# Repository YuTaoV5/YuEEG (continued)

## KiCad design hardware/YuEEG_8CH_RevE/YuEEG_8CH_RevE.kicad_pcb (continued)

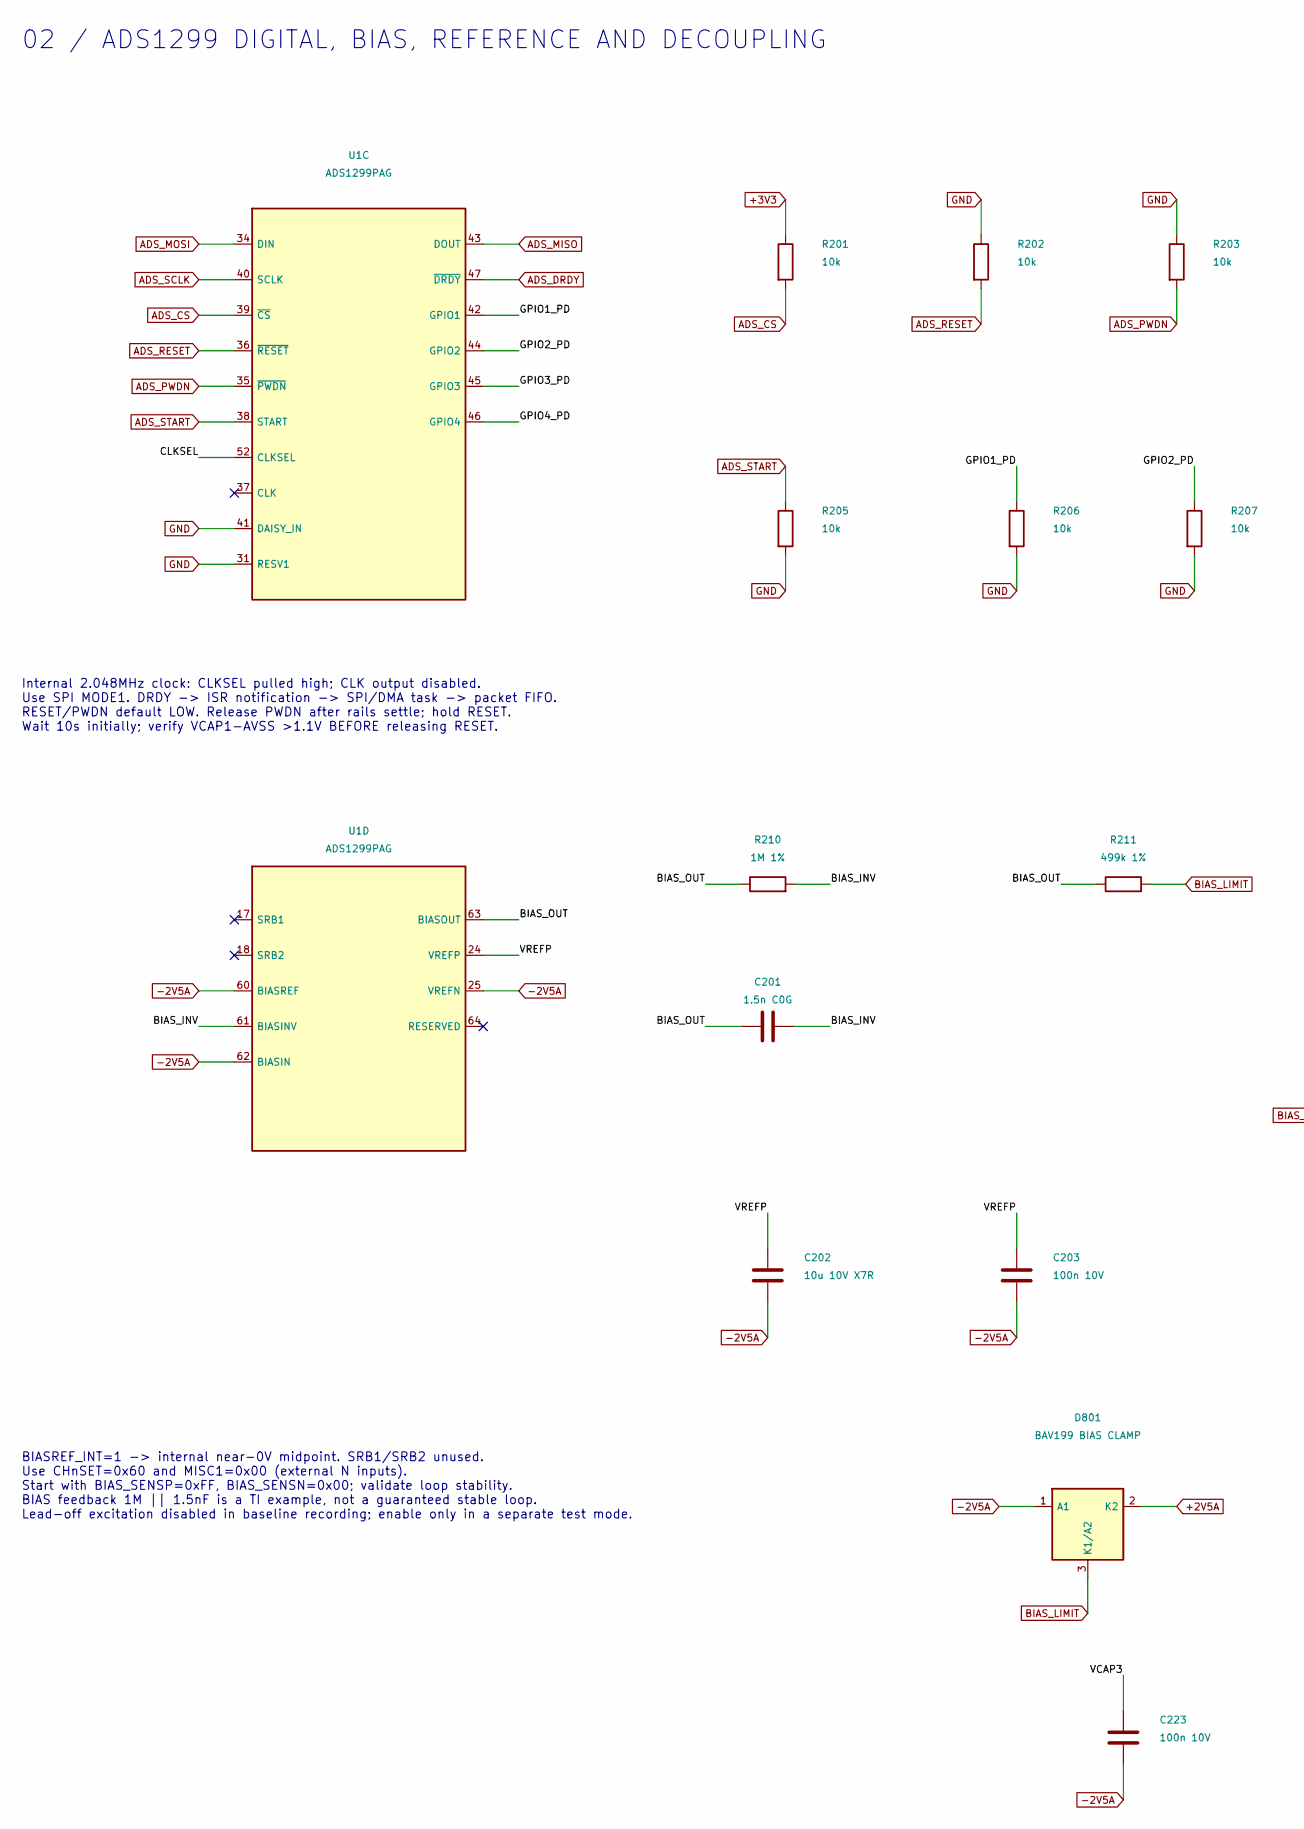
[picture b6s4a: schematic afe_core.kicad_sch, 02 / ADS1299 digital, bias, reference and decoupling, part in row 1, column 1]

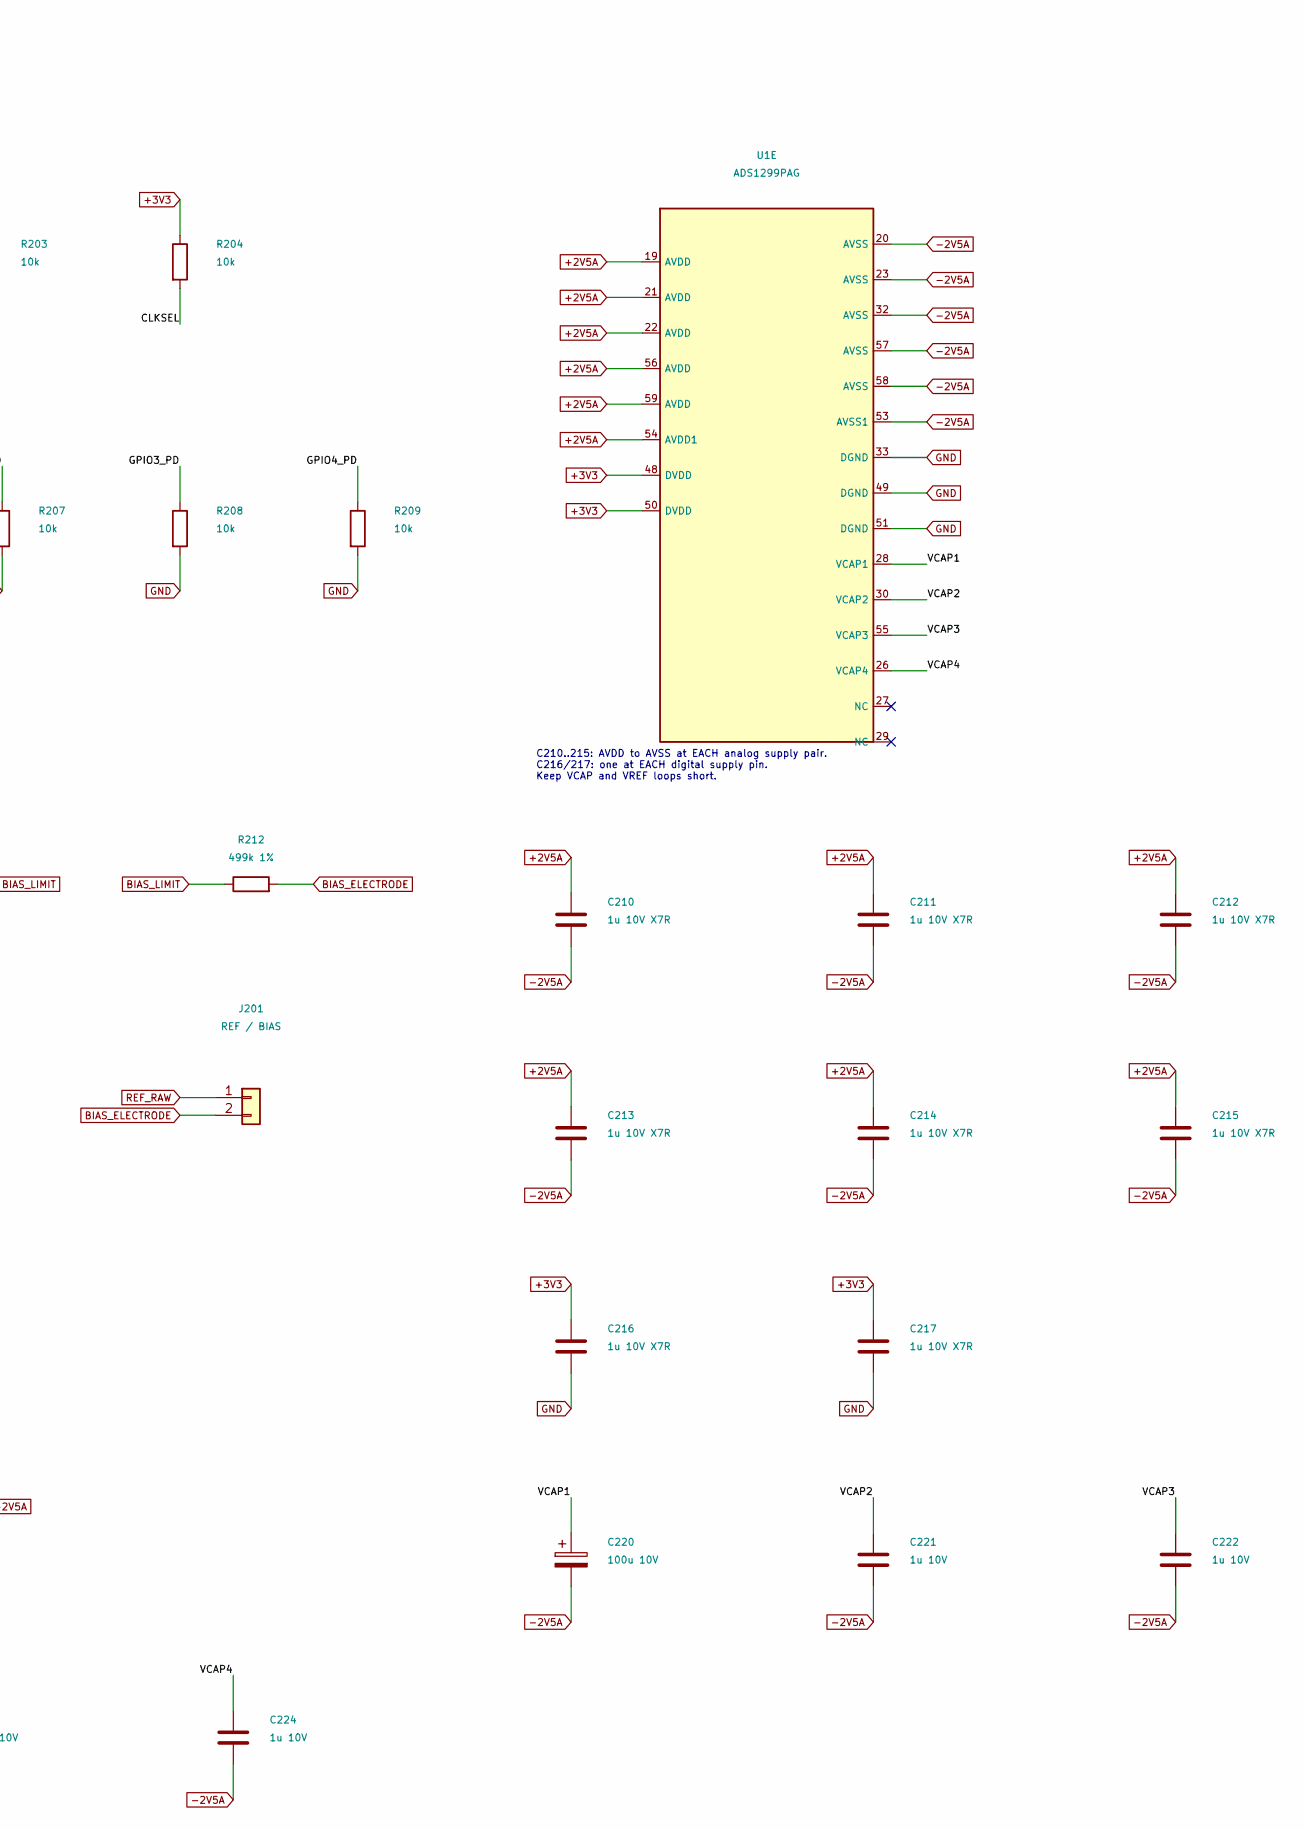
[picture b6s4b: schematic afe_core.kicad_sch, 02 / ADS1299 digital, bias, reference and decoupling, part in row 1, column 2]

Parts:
C201: 1.5n C0G; C_0603_1608Metric
C202: 10u 10V X7R; C_0805_2012Metric
C203, C223: 100n 10V; C_0603_1608Metric
C210, C211, C212, C213, C214, C215, C216, C217: 1u 10V X7R; C_0603_1608Metric
C220: 100u 10V; CP_Elec_6.3x7.7
C221, C222, C224: 1u 10V; C_0603_1608Metric
D801: BAV199 BIAS CLAMP; SOT-23
J201: REF / BIAS; PinHeader_1x02_P2.54mm_Vertical
R201, R202, R203, R204, R205, R206, R207, R208, R209: 10k; R_0603_1608Metric
R210: 1M 1%; R_0603_1608Metric
R211, R212: 499k 1%; R_0603_1608Metric
U1: ADS1299PAG; TQFP-64_10x10mm_P0.5mm

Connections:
+2V5A: C210.1, C211.1, C212.1, C213.1, C214.1, C215.1, D801.2 (K2), U1.19 (AVDD), U1.21 (AVDD), U1.22 (AVDD), U1.54 (AVDD1), U1.56 (AVDD), U1.59 (AVDD); also elsewhere on the board
+3V3: C216.1, C217.1, R201.1, R204.1, U1.48 (DVDD), U1.50 (DVDD); also elsewhere on the board
-2V5A: C202.2, C203.2, C210.2, C211.2, C212.2, C213.2, C214.2, C215.2, C220.2, C221.2, C222.2, C223.2, C224.2, D801.1 (A1), U1.20 (AVSS), U1.23 (AVSS), U1.25 (VREFN), U1.32 (AVSS), U1.53 (AVSS1), U1.57 (AVSS), U1.58 (AVSS), U1.60 (BIASREF), U1.62 (BIASIN); also elsewhere on the board
/02 / ADS1299 digital, bias, reference and decoupling/BIAS_INV: C201.2, R210.2, U1.61 (BIASINV)
/02 / ADS1299 digital, bias, reference and decoupling/BIAS_OUT: C201.1, R210.1, R211.1, U1.63 (BIASOUT)
/02 / ADS1299 digital, bias, reference and decoupling/CLKSEL: R204.2, U1.52 (CLKSEL)
/02 / ADS1299 digital, bias, reference and decoupling/GPIO1_PD: R206.1, U1.42 (GPIO1)
/02 / ADS1299 digital, bias, reference and decoupling/GPIO2_PD: R207.1, U1.44 (GPIO2)
/02 / ADS1299 digital, bias, reference and decoupling/GPIO3_PD: R208.1, U1.45 (GPIO3)
/02 / ADS1299 digital, bias, reference and decoupling/GPIO4_PD: R209.1, U1.46 (GPIO4)
/02 / ADS1299 digital, bias, reference and decoupling/VCAP1: C220.1, U1.28 (VCAP1)
/02 / ADS1299 digital, bias, reference and decoupling/VCAP2: C221.1, U1.30 (VCAP2)
/02 / ADS1299 digital, bias, reference and decoupling/VCAP3: C222.1, C223.1, U1.55 (VCAP3)
/02 / ADS1299 digital, bias, reference and decoupling/VCAP4: C224.1, U1.26 (VCAP4)
/02 / ADS1299 digital, bias, reference and decoupling/VREFP: C202.1, C203.1, U1.24 (VREFP)
ADS_CS: R201.2, U1.39 (~CS); also elsewhere on the board
ADS_DRDY: U1.47 (~DRDY); also elsewhere on the board
ADS_MISO: U1.43 (DOUT); also elsewhere on the board
ADS_MOSI: U1.34 (DIN); also elsewhere on the board
ADS_PWDN: R203.2, U1.35 (~PWDN); also elsewhere on the board
ADS_RESET: R202.2, U1.36 (~RESET); also elsewhere on the board
ADS_SCLK: U1.40 (SCLK); also elsewhere on the board
ADS_START: R205.1, U1.38 (START); also elsewhere on the board
BIAS_ELECTRODE: J201.2, R212.2
BIAS_LIMIT: D801.3 (K1/A2), R211.2, R212.1
GND: C216.2, C217.2, R202.1, R203.1, R205.2, R206.2, R207.2, R208.2, R209.2, U1.31 (RESV1), U1.33 (DGND), U1.41 (DAISY_IN), U1.49 (DGND), U1.51 (DGND); also elsewhere on the board
REF_RAW: J201.1; also elsewhere on the board

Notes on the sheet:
02 / ADS1299 DIGITAL, BIAS, REFERENCE AND DECOUPLING
Internal 2.048MHz clock: CLKSEL pulled high; CLK output disabled. Use SPI MODE1. DRDY -> ISR notification -> SPI/DMA task -> packet FIFO. RESET/PWDN default LOW. Release PWDN after rails settle; hold RESET. Wait 10s initially; verify VCAP1-AVSS >1.1V BEFORE releasing RESET.
BIASREF_INT=1 -> internal near-0V midpoint. SRB1/SRB2 unused. Use CHnSET=0x60 and MISC1=0x00 (external N inputs). Start with BIAS_SENSP=0xFF, BIAS_SENSN=0x00; validate loop stability. BIAS feedback 1M || 1.5nF is a TI example, not a guaranteed stable loop. Lead-off excitation disabled in baseline r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
C210..215: AVDD to AVSS at EACH analog supply pair. C216/217: one at EACH digital supply pin. Keep VCAP and VREF loops short.

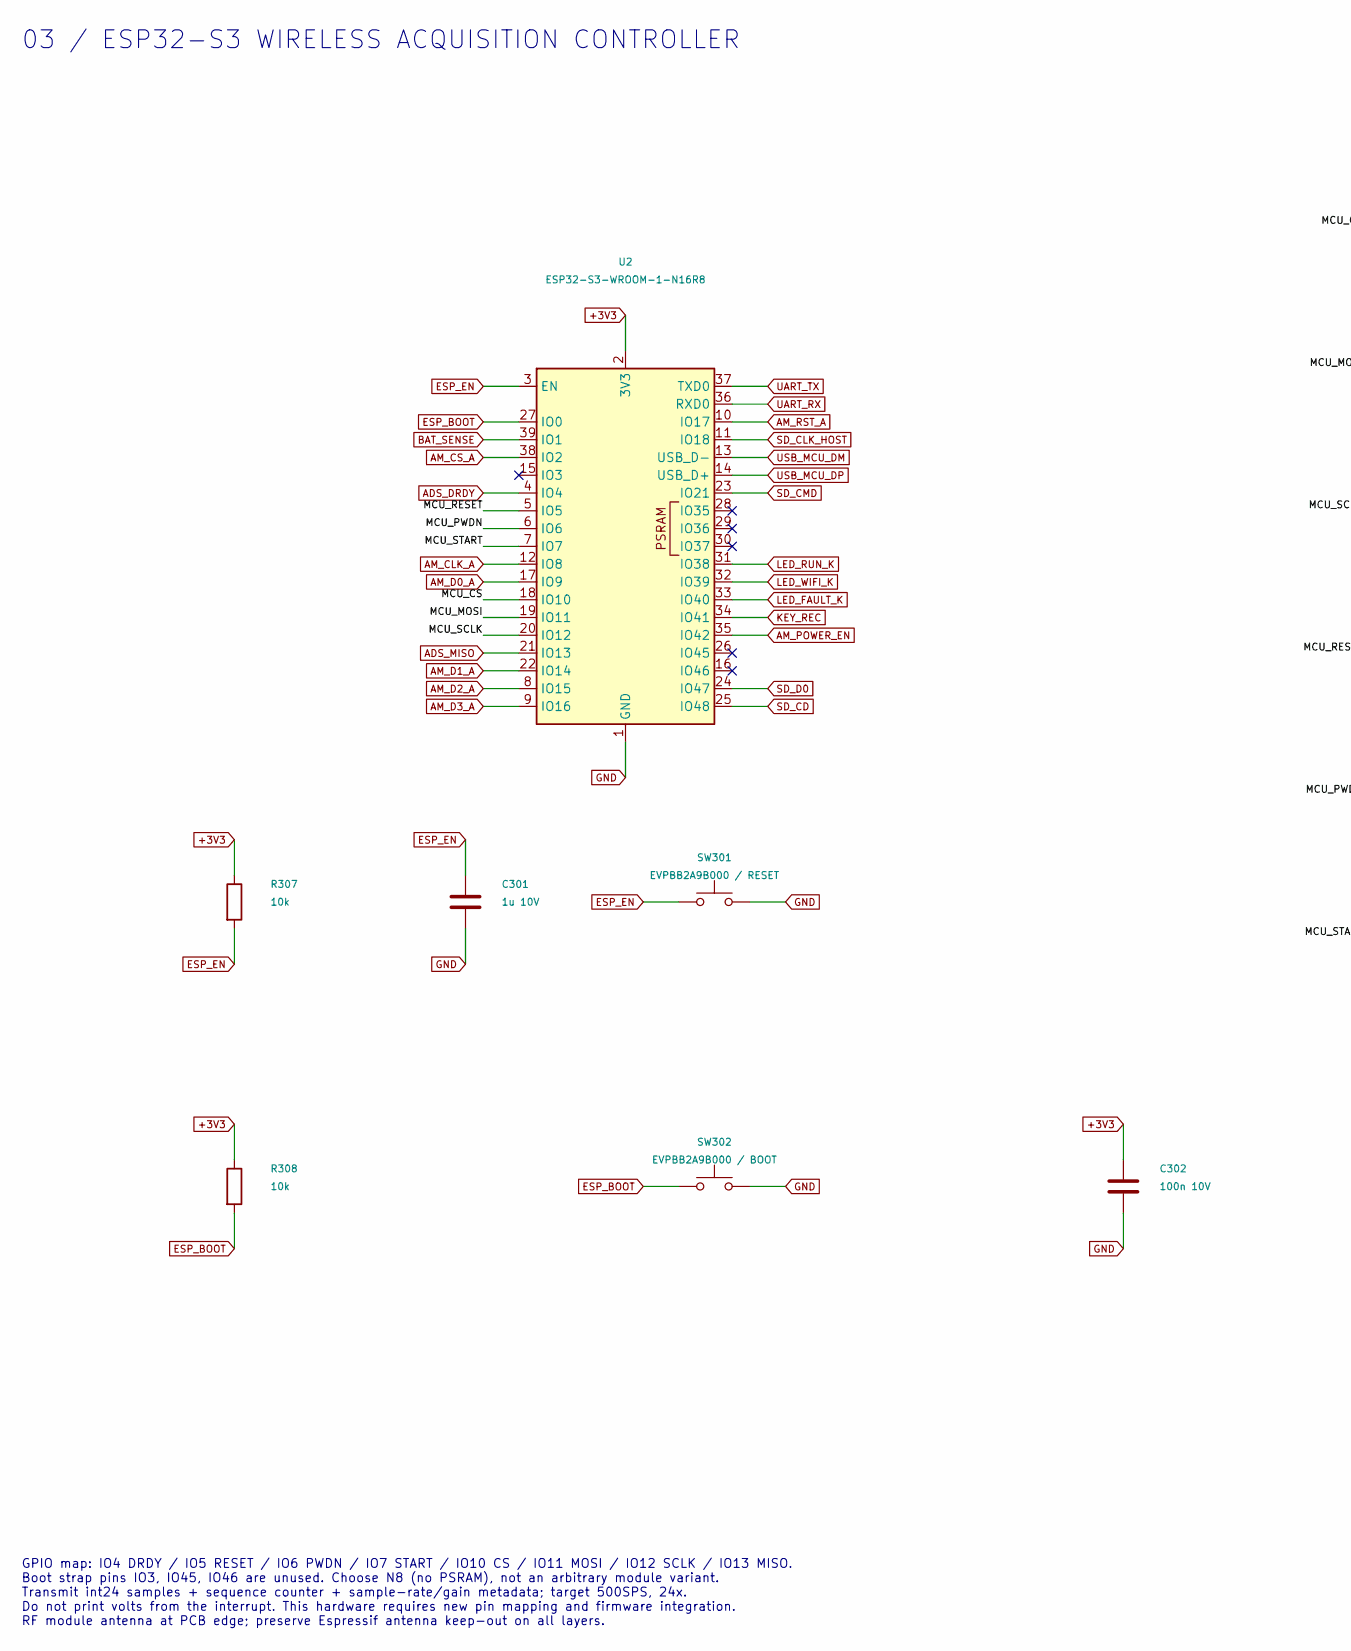
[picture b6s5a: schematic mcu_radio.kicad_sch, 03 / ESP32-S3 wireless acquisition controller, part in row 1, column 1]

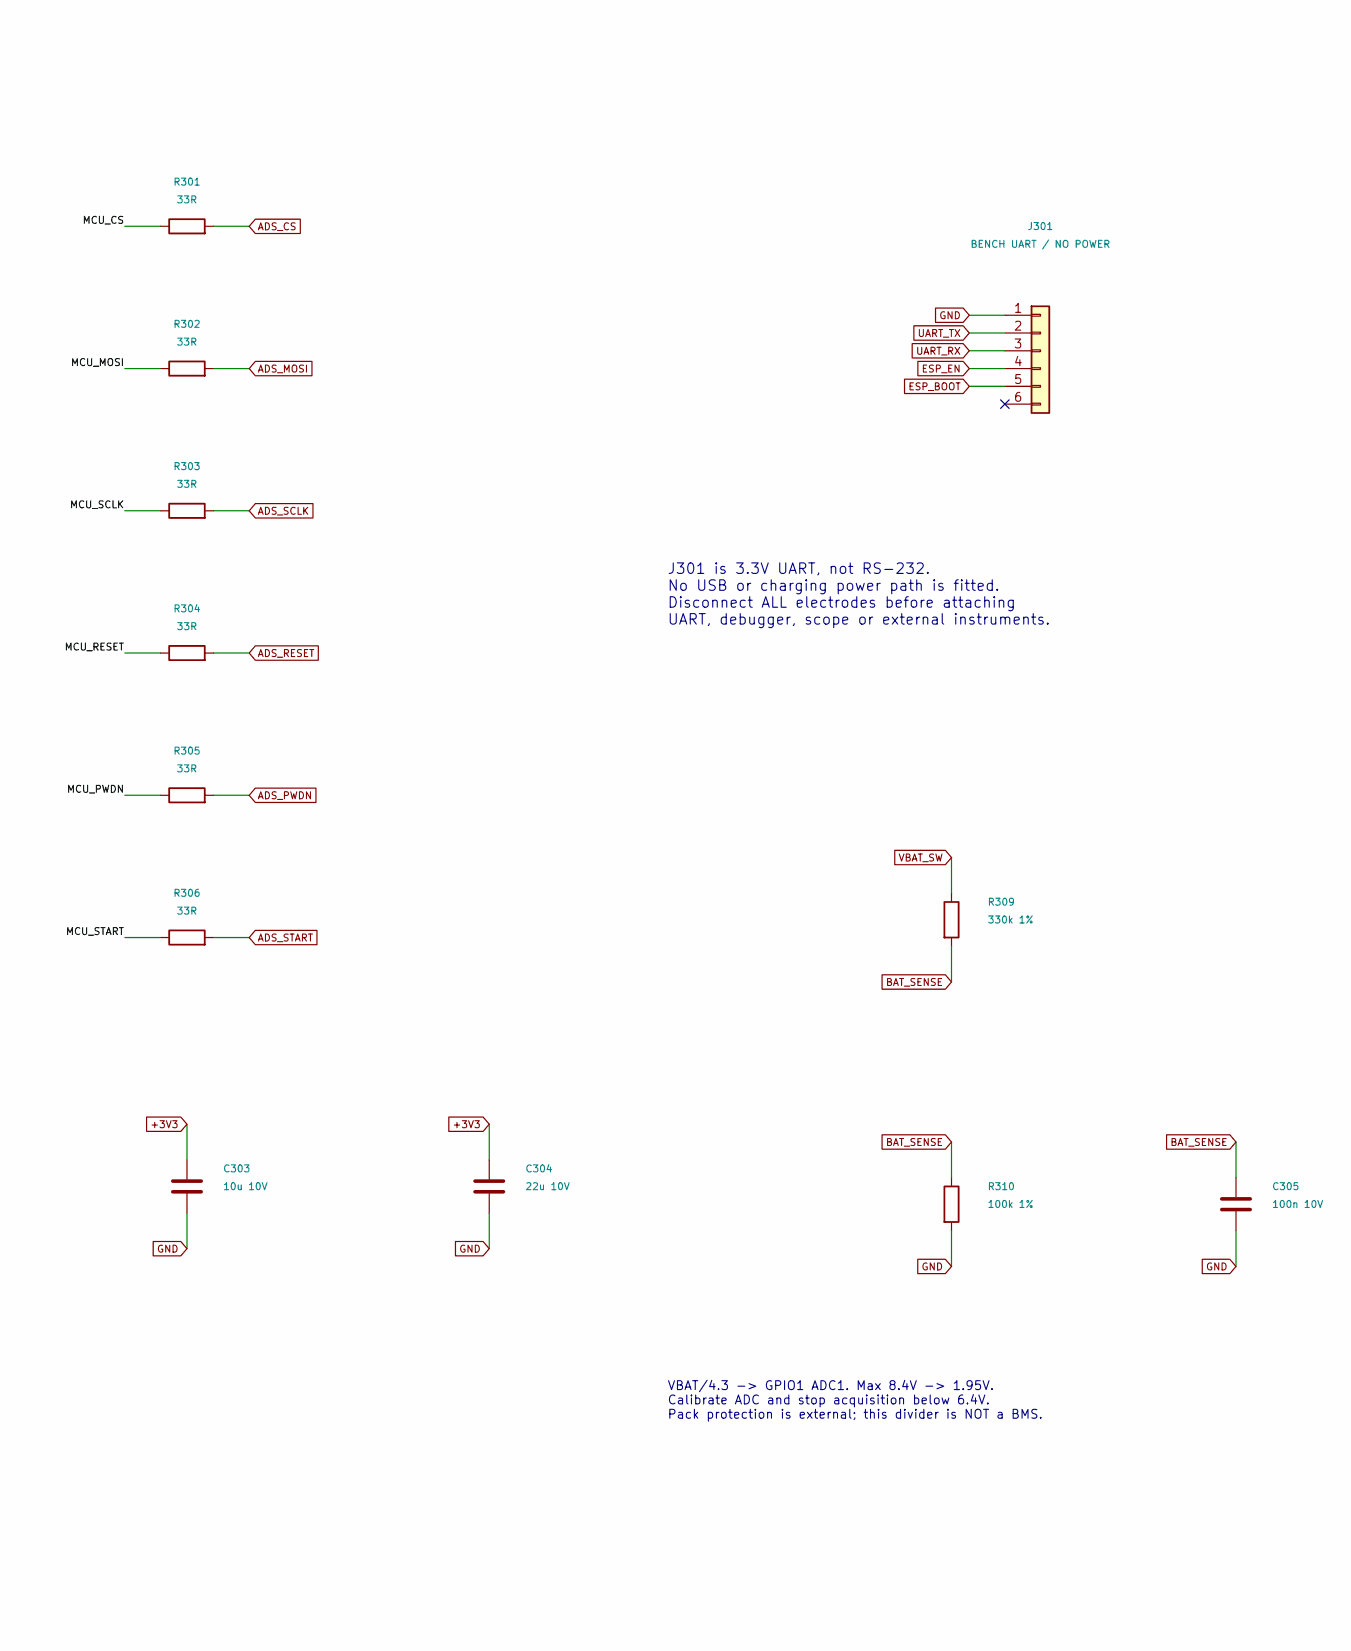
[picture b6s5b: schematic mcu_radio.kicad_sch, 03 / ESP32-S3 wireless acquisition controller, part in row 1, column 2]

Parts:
C301: 1u 10V; C_0603_1608Metric
C302: 100n 10V; C_0805_2012Metric
C303: 10u 10V; C_0805_2012Metric
C304: 22u 10V; C_0805_2012Metric
C305: 100n 10V; C_0603_1608Metric
J301: BENCH UART / NO POWER; PinHeader_1x06_P2.54mm_Vertical
R301, R302, R303, R304, R305, R306: 33R; R_0603_1608Metric
R307, R308: 10k; R_0603_1608Metric
R309: 330k 1%; R_0603_1608Metric
R310: 100k 1%; R_0603_1608Metric
SW301: EVPBB2A9B000 / RESET; EVPBB_2p6x1p6_H0p53
SW302: EVPBB2A9B000 / BOOT; EVPBB_2p6x1p6_H0p53
U2: ESP32-S3-WROOM-1-N16R8; ESP32-S3-WROOM-1

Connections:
+3V3: C302.1, C303.1, C304.1, R307.1, R308.1, U2.2 (3V3); also elsewhere on the board
/03 / ESP32-S3 wireless acquisition controller/MCU_CS: R301.1, U2.18 (IO10)
/03 / ESP32-S3 wireless acquisition controller/MCU_MOSI: R302.1, U2.19 (IO11)
/03 / ESP32-S3 wireless acquisition controller/MCU_PWDN: R305.1, U2.6 (IO6)
/03 / ESP32-S3 wireless acquisition controller/MCU_RESET: R304.1, U2.5 (IO5)
/03 / ESP32-S3 wireless acquisition controller/MCU_SCLK: R303.1, U2.20 (IO12)
/03 / ESP32-S3 wireless acquisition controller/MCU_START: R306.1, U2.7 (IO7)
ADS_CS: R301.2; also elsewhere on the board
ADS_DRDY: U2.4 (IO4); also elsewhere on the board
ADS_MISO: U2.21 (IO13); also elsewhere on the board
ADS_MOSI: R302.2; also elsewhere on the board
ADS_PWDN: R305.2; also elsewhere on the board
ADS_RESET: R304.2; also elsewhere on the board
ADS_SCLK: R303.2; also elsewhere on the board
ADS_START: R306.2; also elsewhere on the board
AM_CLK_A: U2.12 (IO8); also elsewhere on the board
AM_CS_A: U2.38 (IO2); also elsewhere on the board
AM_D0_A: U2.17 (IO9); also elsewhere on the board
AM_D1_A: U2.22 (IO14); also elsewhere on the board
AM_D2_A: U2.8 (IO15); also elsewhere on the board
AM_D3_A: U2.9 (IO16); also elsewhere on the board
AM_POWER_EN: U2.35 (IO42); also elsewhere on the board
AM_RST_A: U2.10 (IO17); also elsewhere on the board
BAT_SENSE: C305.1, R309.2, R310.1, U2.39 (IO1)
ESP_BOOT: J301.5, R308.2, SW302.1, U2.27 (IO0)
ESP_EN: C301.1, J301.4, R307.2, SW301.1, U2.3 (EN)
GND: C301.2, C302.2, C303.2, C304.2, C305.2, J301.1, R310.2, SW301.2, SW302.2, U2.1 (GND), U2.40 (GND), U2.41 (GND); also elsewhere on the board
KEY_REC: U2.34 (IO41); also elsewhere on the board
LED_FAULT_K: U2.33 (IO40); also elsewhere on the board
LED_RUN_K: U2.31 (IO38); also elsewhere on the board
LED_WIFI_K: U2.32 (IO39); also elsewhere on the board
SD_CD: U2.25 (IO48); also elsewhere on the board
SD_CLK_HOST: U2.11 (IO18); also elsewhere on the board
SD_CMD: U2.23 (IO21); also elsewhere on the board
SD_D0: U2.24 (IO47); also elsewhere on the board
UART_RX: J301.3, U2.36 (RXD0)
UART_TX: J301.2, U2.37 (TXD0)
USB_MCU_DM: U2.13 (USB_D-); also elsewhere on the board
USB_MCU_DP: U2.14 (USB_D+); also elsewhere on the board
VBAT_SW: R309.1; also elsewhere on the board

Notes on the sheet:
03 / ESP32-S3 WIRELESS ACQUISITION CONTROLLER
J301 is 3.3V UART, not RS-232. No USB or charging power path is fitted. Disconnect ALL electrodes before attaching UART, debugger, scope or external instruments.
VBAT/4.3 -> GPIO1 ADC1. Max 8.4V -> 1.95V. Calibrate ADC and stop acquisition below 6.4V. Pack protection is external; this divider is NOT a BMS.
GPIO map: IO4 DRDY / IO5 RESET / IO6 PWDN / IO7 START / IO10 CS / IO11 MOSI / IO12 SCLK / IO13 MISO. Boot strap pins IO3, IO45, IO46 are unused. Choose N8 (no PSRAM), not an arbitrary module variant. Transmit int24 samples + sequence counter + sample-rate/gain metadata; target 500SPS, 24x. Do not p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

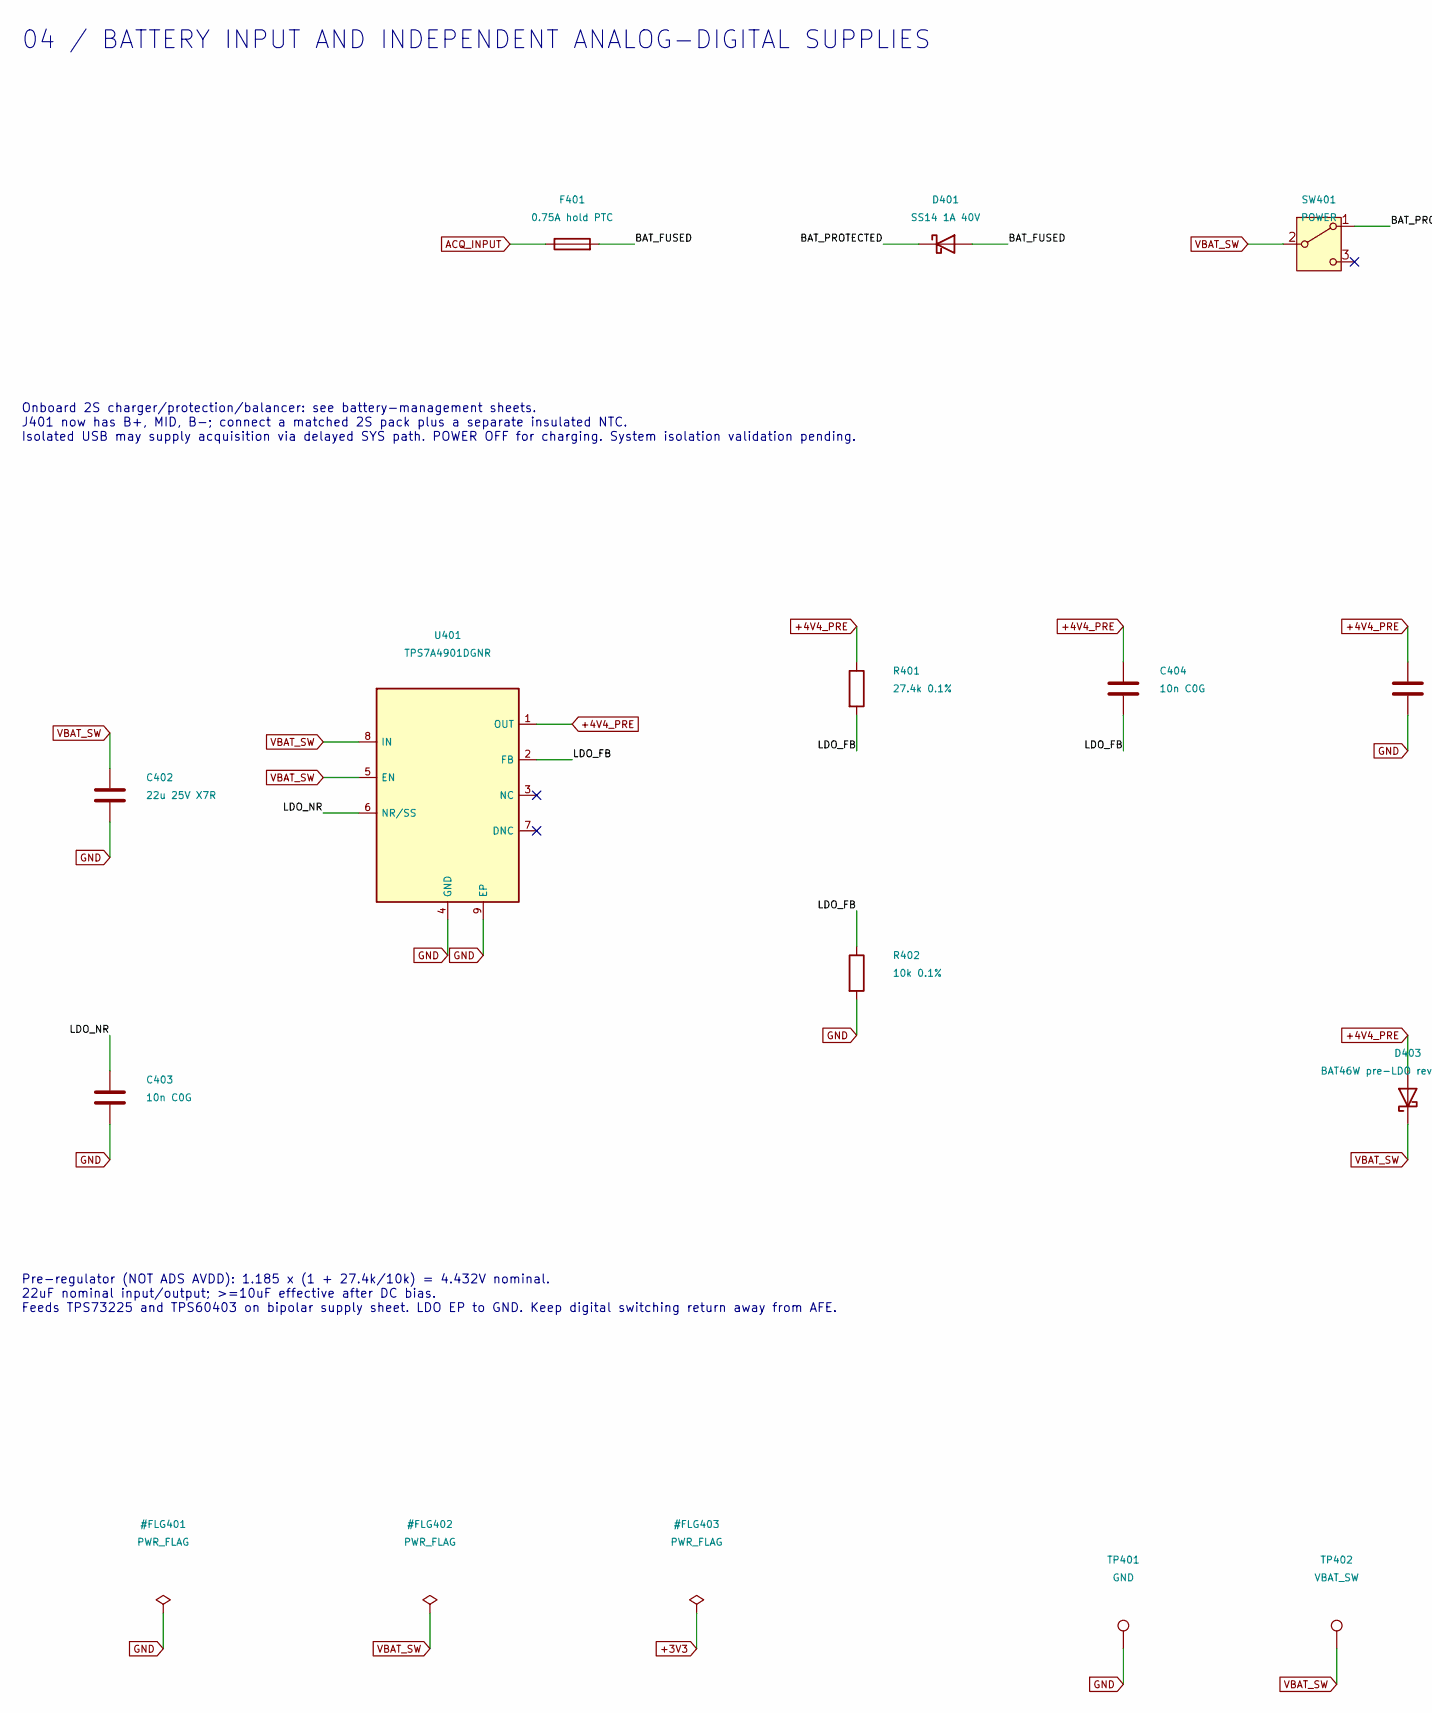
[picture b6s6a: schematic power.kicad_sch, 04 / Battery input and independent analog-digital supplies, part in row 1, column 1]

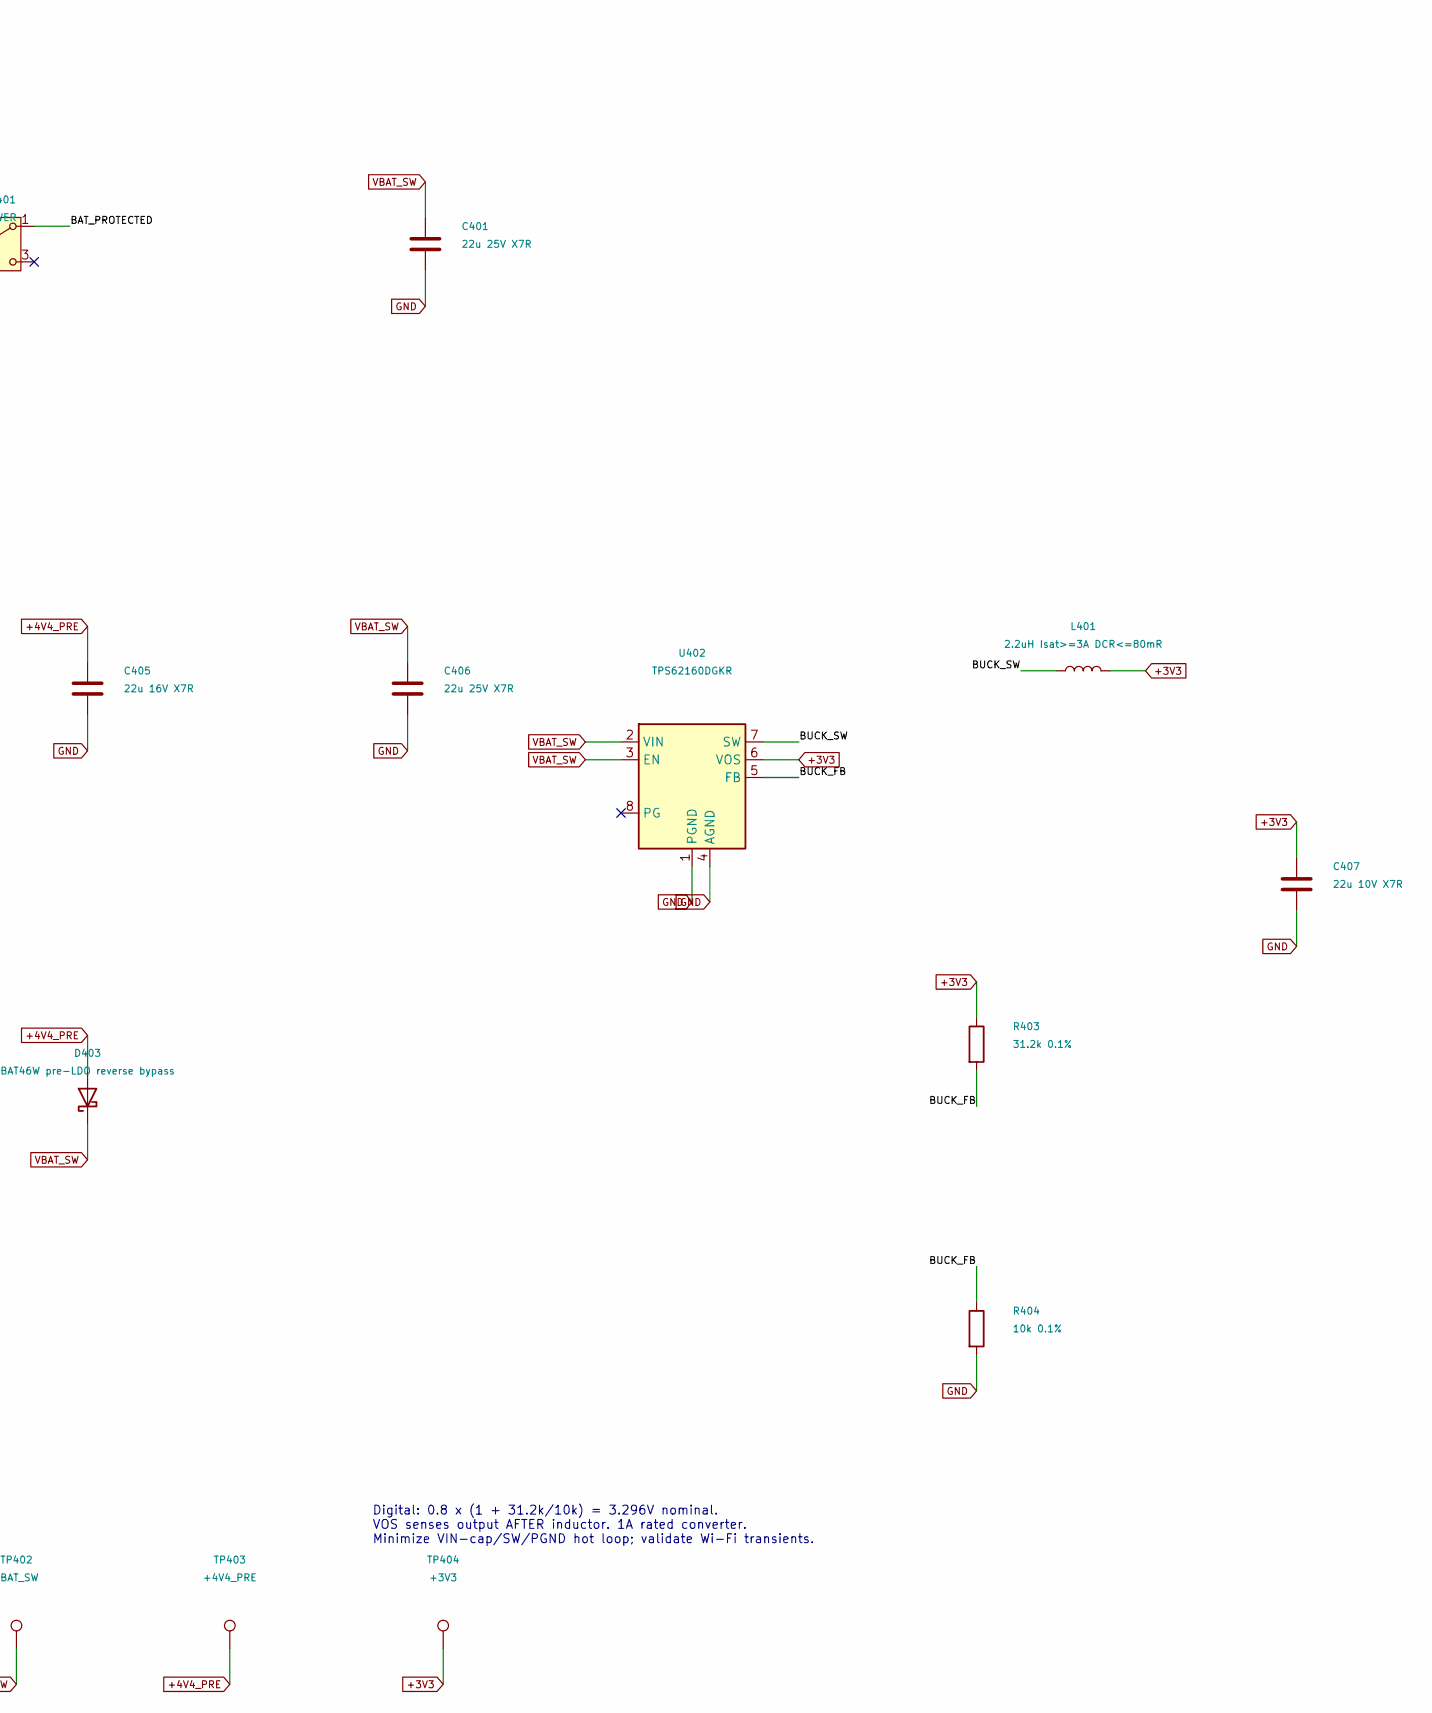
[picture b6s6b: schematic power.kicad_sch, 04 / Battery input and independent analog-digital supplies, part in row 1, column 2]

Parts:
C401, C402, C406: 22u 25V X7R; C_1206_3216Metric
C403, C404: 10n C0G; C_0603_1608Metric
C405: 22u 16V X7R; C_1206_3216Metric
C407: 22u 10V X7R; C_1206_3216Metric
D401: SS14 1A 40V; D_SMA
D403: BAT46W pre-LDO reverse bypass; D_SOD-123
F401: 0.75A hold PTC; Fuse_1206_3216Metric
L401: 2.2uH Isat>=3A DCR<=80mR; L_Taiyo-Yuden_NR-40xx
R401: 27.4k 0.1%; R_0603_1608Metric
R402, R404: 10k 0.1%; R_0603_1608Metric
R403: 31.2k 0.1%; R_0603_1608Metric
SW401: POWER; SW_SPDT_CK_JS102011SAQN
TP401: GND; TestPoint_Pad_D1.5mm
TP402: VBAT_SW; TestPoint_Pad_D1.5mm
TP403: +4V4_PRE; TestPoint_Pad_D1.5mm
TP404: +3V3; TestPoint_Pad_D1.5mm
U401: TPS7A4901DGNR; HVSSOP-8-1EP_3x3mm_P0.65mm_EP1.57x1.89mm
U402: TPS62160DGKR; MSOP-8_3x3mm_P0.65mm

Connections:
+3V3: C407.1, L401.2, R403.1, TP404.1, U402.6 (VOS); also elsewhere on the board
+4V4_PRE: C404.1, C405.1, D403.2 (A), R401.1, TP403.1, U401.1 (OUT); also elsewhere on the board
/04 / Battery input and independent analog-digital supplies/BAT_FUSED: D401.2 (A), F401.2
/04 / Battery input and independent analog-digital supplies/BAT_PROTECTED: D401.1 (K), SW401.1 (A)
/04 / Battery input and independent analog-digital supplies/BUCK_FB: R403.2, R404.1, U402.5 (FB)
/04 / Battery input and independent analog-digital supplies/BUCK_SW: L401.1, U402.7 (SW)
/04 / Battery input and independent analog-digital supplies/LDO_FB: C404.2, R401.2, R402.1, U401.2 (FB)
/04 / Battery input and independent analog-digital supplies/LDO_NR: C403.1, U401.6 (NR/SS)
ACQ_INPUT: F401.1; also elsewhere on the board
GND: C401.2, C402.2, C403.2, C405.2, C406.2, C407.2, R402.2, R404.2, TP401.1, U401.4 (GND), U401.9 (EP), U402.1 (PGND), U402.4 (AGND); also elsewhere on the board
VBAT_SW: C401.1, C402.1, C406.1, D403.1 (K), SW401.2 (B), TP402.1, U401.5 (EN), U401.8 (IN), U402.2 (VIN), U402.3 (EN); also elsewhere on the board

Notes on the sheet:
04 / BATTERY INPUT AND INDEPENDENT ANALOG-DIGITAL SUPPLIES
Onboard 2S charger/protection/balancer: see battery-management sheets. J401 now has B+, MID, B-; connect a matched 2S pack plus a separate insulated NTC. Isolated USB may supply acquisition via delayed SYS path. POWER OFF for charging. System isolation validation pending.
Pre-regulator (NOT ADS AVDD): 1.185 x (1 + 27.4k/10k) = 4.432V nominal. 22uF nominal input/output; >=10uF effective after DC bias. Feeds TPS73225 and TPS60403 on bipolar supply sheet. LDO EP to GND. Keep digital switching return away from AFE.
Digital: 0.8 x (1 + 31.2k/10k) = 3.296V nominal. VOS senses output AFTER inductor. 1A rated converter. Minimize VIN-cap/SW/PGND hot loop; validate Wi-Fi transients.
